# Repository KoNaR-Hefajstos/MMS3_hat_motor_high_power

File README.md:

# Hat Motor High Power

Dostosowany do 48V, ale można zmienić XXX żeby pracować na większym napięciu aż do 100V

Up to 100V 10A

# Dokumentacja
https://github.com/Themuse061/Moducard_System_Handbook

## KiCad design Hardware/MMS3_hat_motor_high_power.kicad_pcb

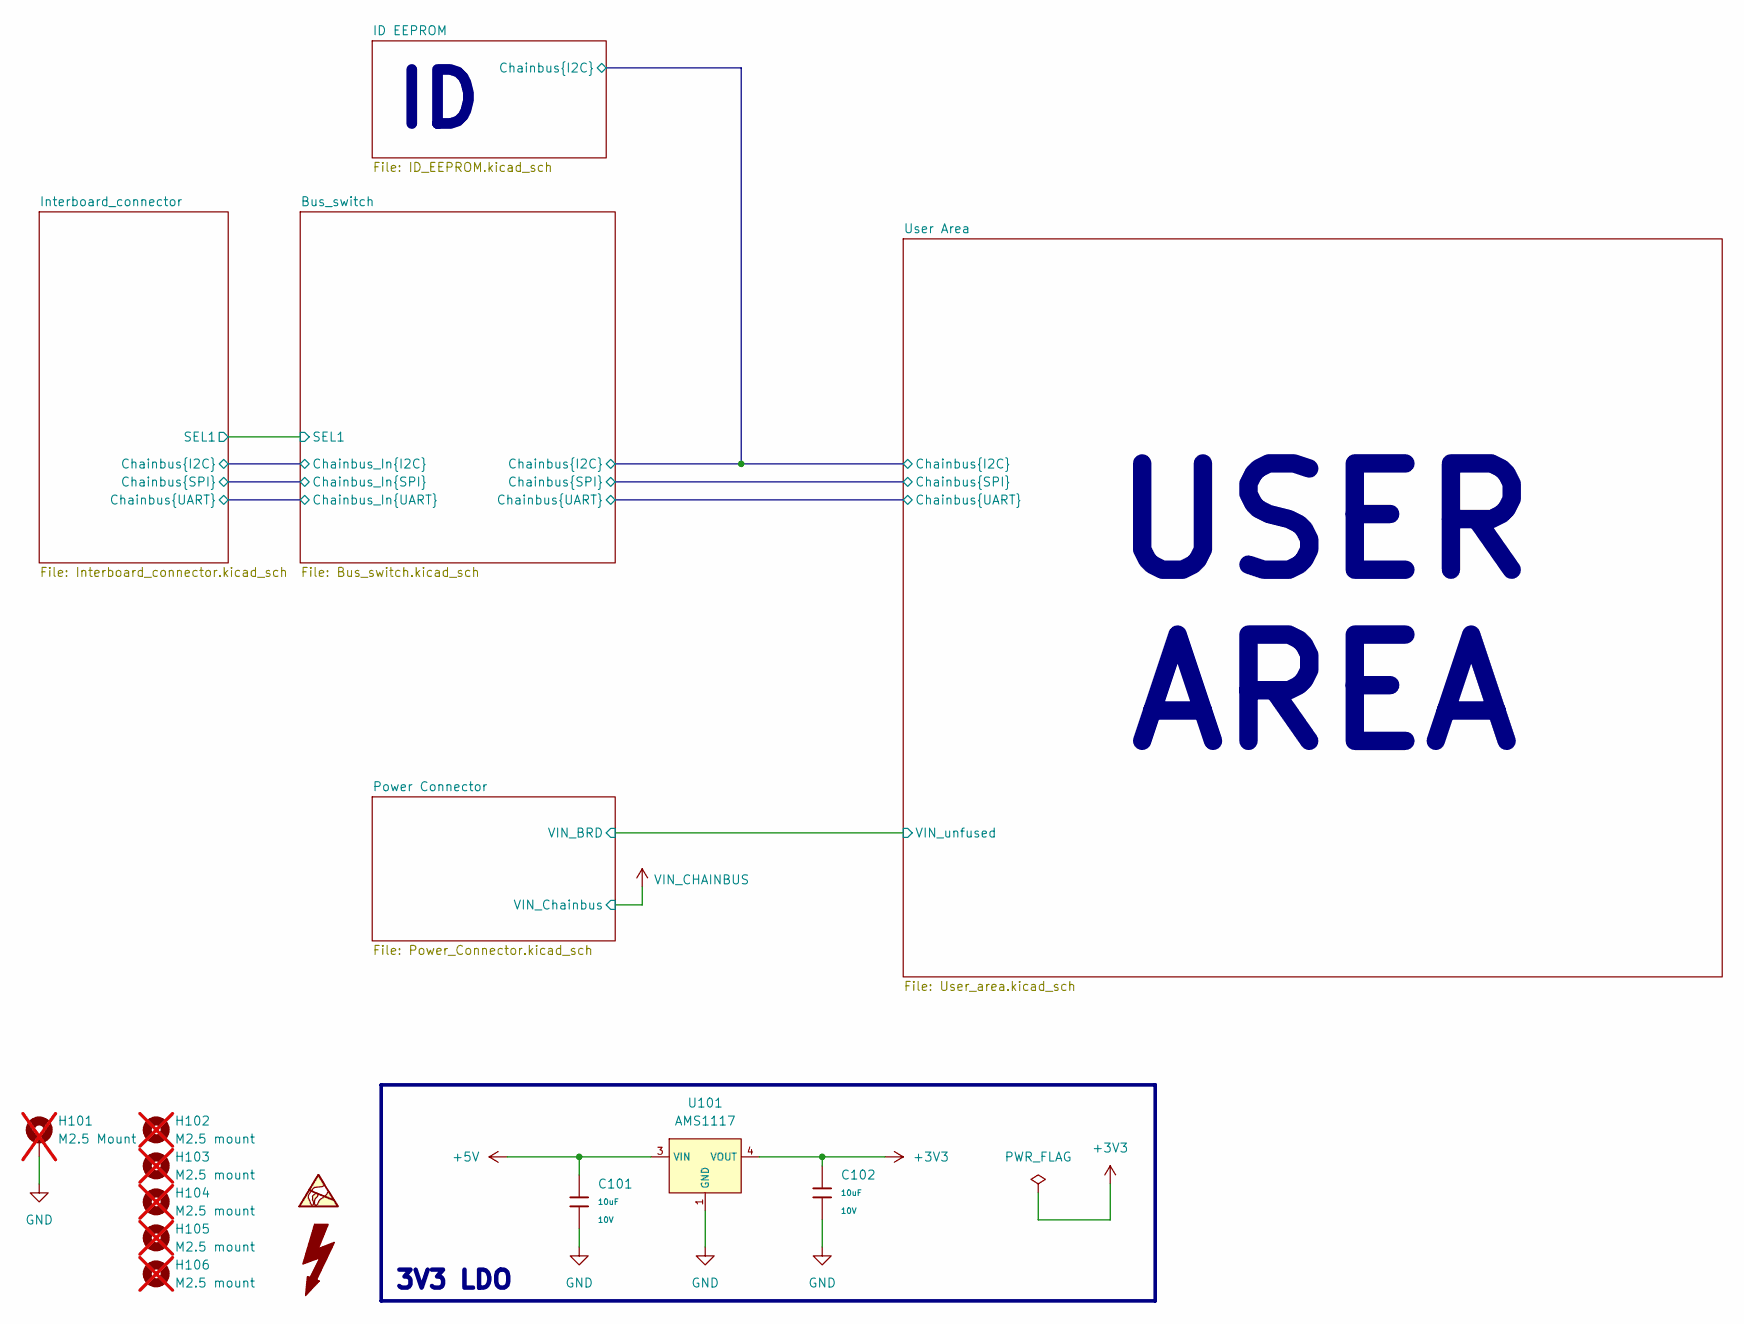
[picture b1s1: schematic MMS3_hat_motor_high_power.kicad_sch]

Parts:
C101, C102: 10uF; C_0603; Voltage Rated 10V; Tolerance ±10%; Part CL10A106KP8NNNC; LCSC C19702
H101: M2.5 Mount; MountingHole_2.7mm_M2.5_DIN965_Pad_TopOnly; not fitted
H102, H103, H104, H105, H106: M2.5 mount; MountingHole_2.7mm_M2.5; not fitted
U101: AMS1117; SOT-223-3_L6.5-W3.4-P2.30-LS7.0-BR; Output Voltage 3.3V; Dropout Voltage 1.3V@(800mA); Part AMS1117-3.3; LCSC C6186

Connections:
+3V3: C102.1, U101.2 (VOUT), U101.4 (VOUT); also elsewhere on the board
+5V: C101.1, U101.3 (VIN); also elsewhere on the board
GND: C101.2, C102.2, H101.1 (1_1), U101.1 (GND); also elsewhere on the board

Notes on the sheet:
USER AREA
3V3 LDO

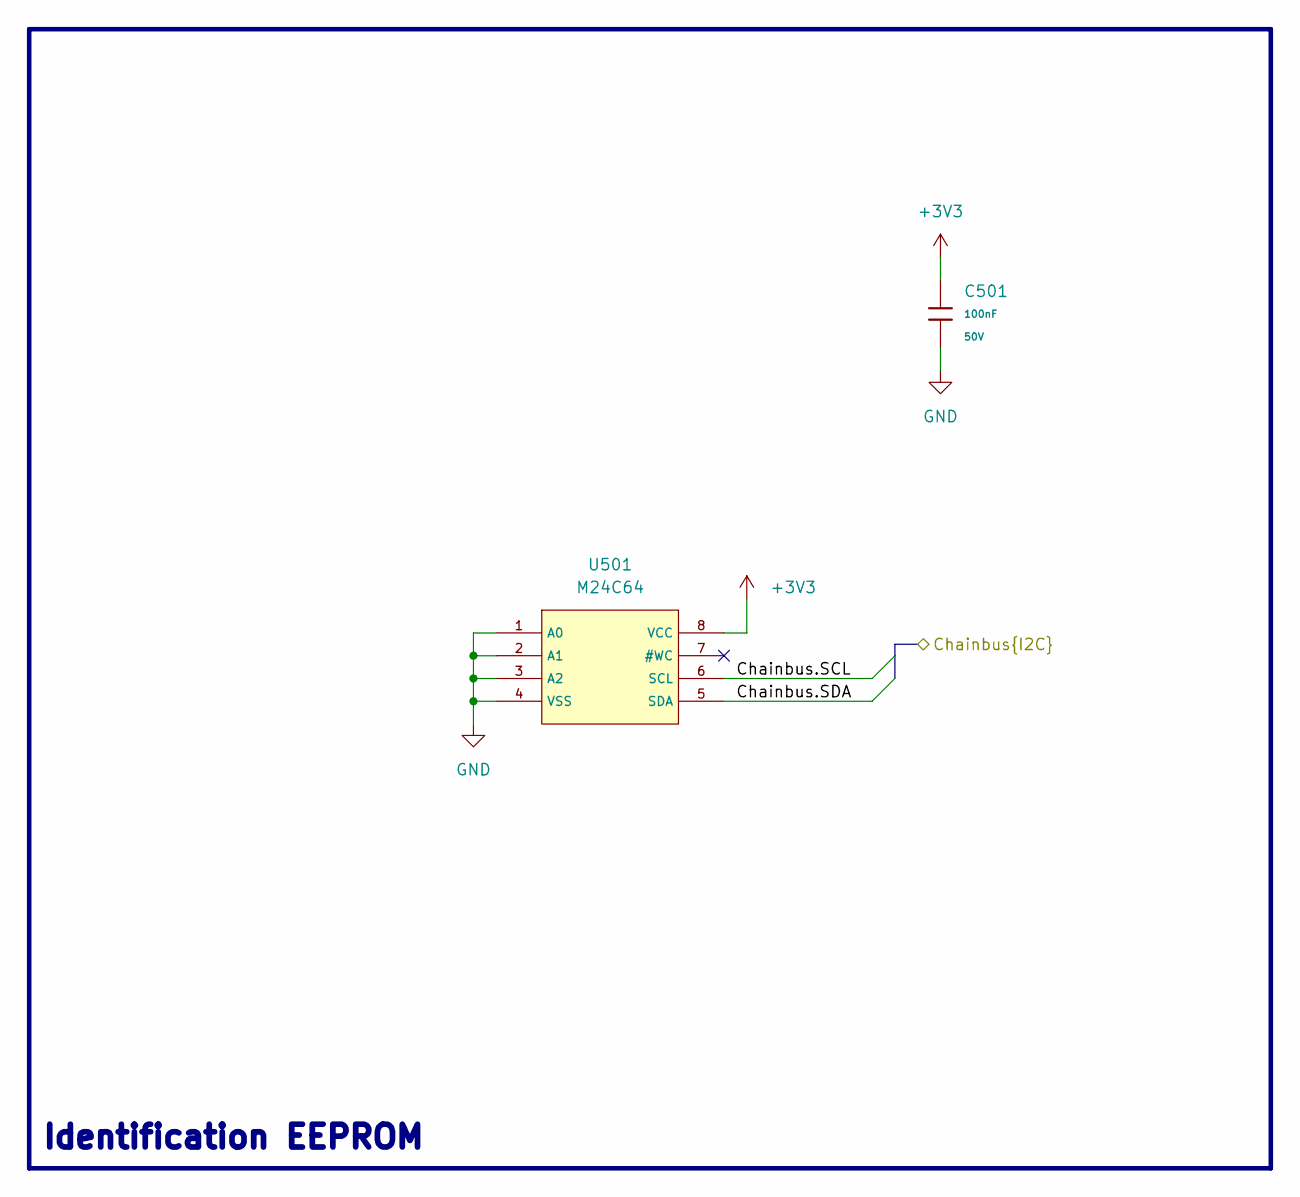
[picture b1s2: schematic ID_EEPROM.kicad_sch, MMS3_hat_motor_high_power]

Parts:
C501: 100nF; C_0603; Voltage Rated 50V; Tolerance ±10%; Part CC0603KRX7R9BB104; LCSC C14663
U501: M24C64; SOIC-8_L5.0-W4.0-P1.27-LS6.0-BL; Supply Voltage 1.8V~5.5V; Part M24C64-RMN6TP; LCSC C79988

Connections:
+3V3: C501.1, U501.8 (VCC); also elsewhere on the board
/Bus_switch/Chainbus.SCL: U501.6 (SCL); also elsewhere on the board
/Bus_switch/Chainbus.SDA: U501.5 (SDA); also elsewhere on the board
GND: C501.2, U501.1 (A0), U501.2 (A1), U501.3 (A2), U501.4 (VSS); also elsewhere on the board

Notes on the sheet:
Identification EEPROM

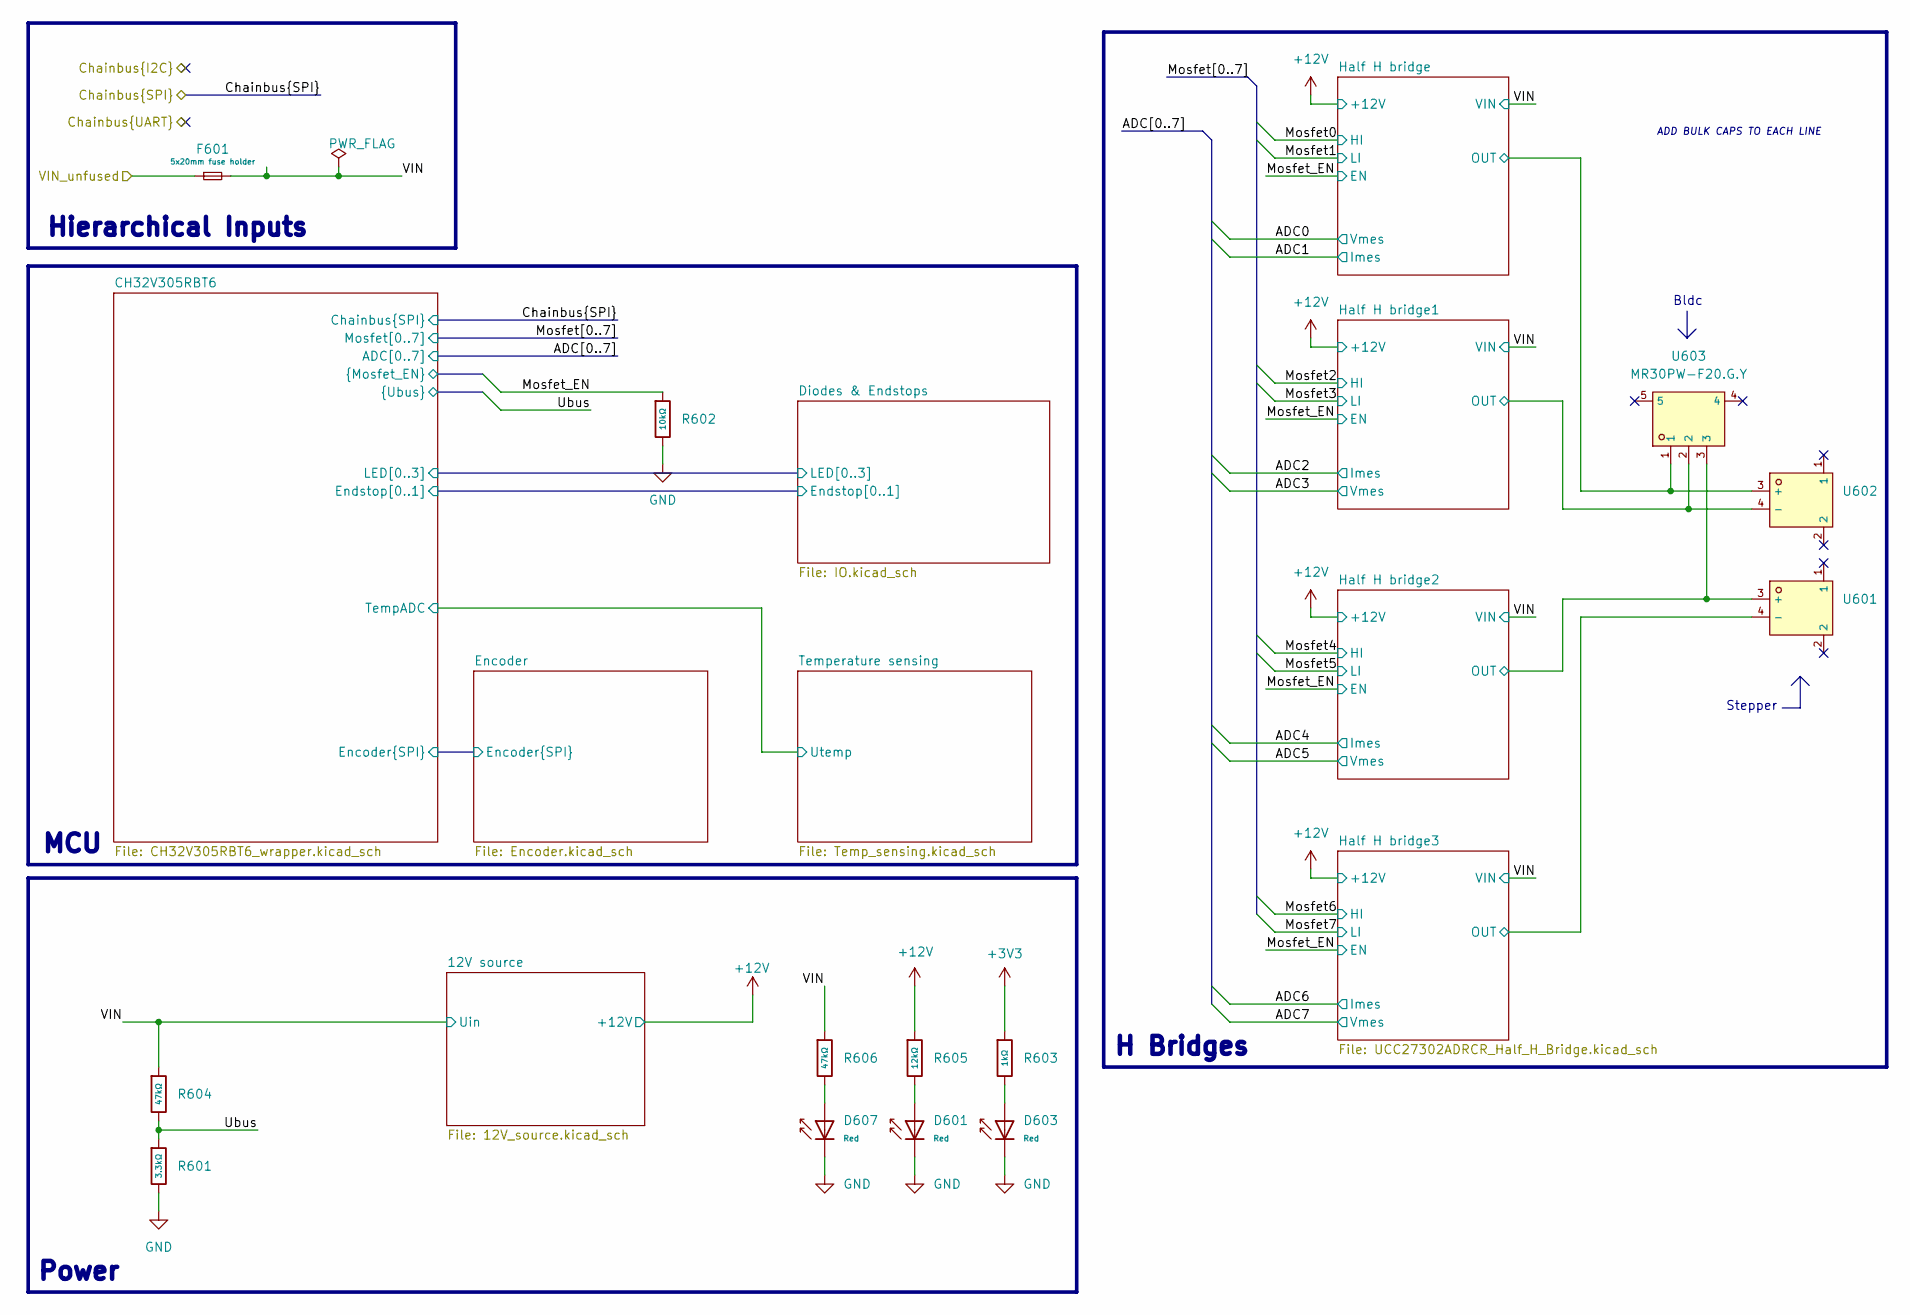
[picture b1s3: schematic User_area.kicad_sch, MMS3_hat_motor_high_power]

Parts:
D601, D603, D607: Red; D_0603; Part KT-0603R; LCSC C2286
F601: 01110506Z; Fuseholder_Clip-5x20mm_Littelfuse_111_Lateral_P18.80x5.00mm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; LCSC C206900
R601: 3.3kΩ; R_0402; Overload Voltage (Max) 50V; Tolerance ±1%; Part 0402WGF3301TCE; LCSC C25890
R602: 10kΩ; R_0402; Overload Voltage (Max) 50V; Tolerance ±1%; Part 0402WGF1002TCE; LCSC C25744
R603: 1kΩ; R_0402; Overload Voltage (Max) 50V; Tolerance ±1%; Part 0402WGF1001TCE; LCSC C11702
R604, R606: 47kΩ; R_0402; Overload Voltage (Max) 50V; Tolerance ±1%; Part 0402WGF4702TCE; LCSC C25792
R605: 12kΩ; R_0402; Overload Voltage (Max) 50V; Tolerance ±1%; Part 0402WGF1202TCE; LCSC C25752
U601, U602: XT60PW-F_C428722; C428722_TH_2P-XT60PW-F; LCSC C428722
U603: MR30PW-F20.G.Y; C19268035_CONN-TH_MR30PW-F; LCSC C19268035

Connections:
+3V3: R603.1; also elsewhere on the board
+12V: R605.1; also elsewhere on the board
/Power Connector/VIN_BRD: F601.1; also elsewhere on the board
/User Area/CH32V305RBT6/GPIOA0: R601.1, R604.2; also elsewhere on the board
/User Area/CH32V305RBT6/GPIOB12: R602.1; also elsewhere on the board
/User Area/Half H bridge1/HS: U602.4 (-), U603.2; also elsewhere on the board
/User Area/Half H bridge2/HS: U601.3 (+), U603.3; also elsewhere on the board
/User Area/Half H bridge3/HS: U601.4 (-); also elsewhere on the board
/User Area/Half H bridge/HS: U602.3 (+), U603.1; also elsewhere on the board
/User Area/VIN: F601.2, R604.1, R606.1; also elsewhere on the board
GND: D601.1, D603.1, D607.1, R601.2, R602.2; also elsewhere on the board
unnamed: D601.2, R605.2
unnamed: D603.2, R603.2
unnamed: D607.2, R606.2

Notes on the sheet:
Hierarchical Inputs
H Bridges
Power
MCU
Stepper
Bldc
ADD BULK CAPS TO EACH LINE

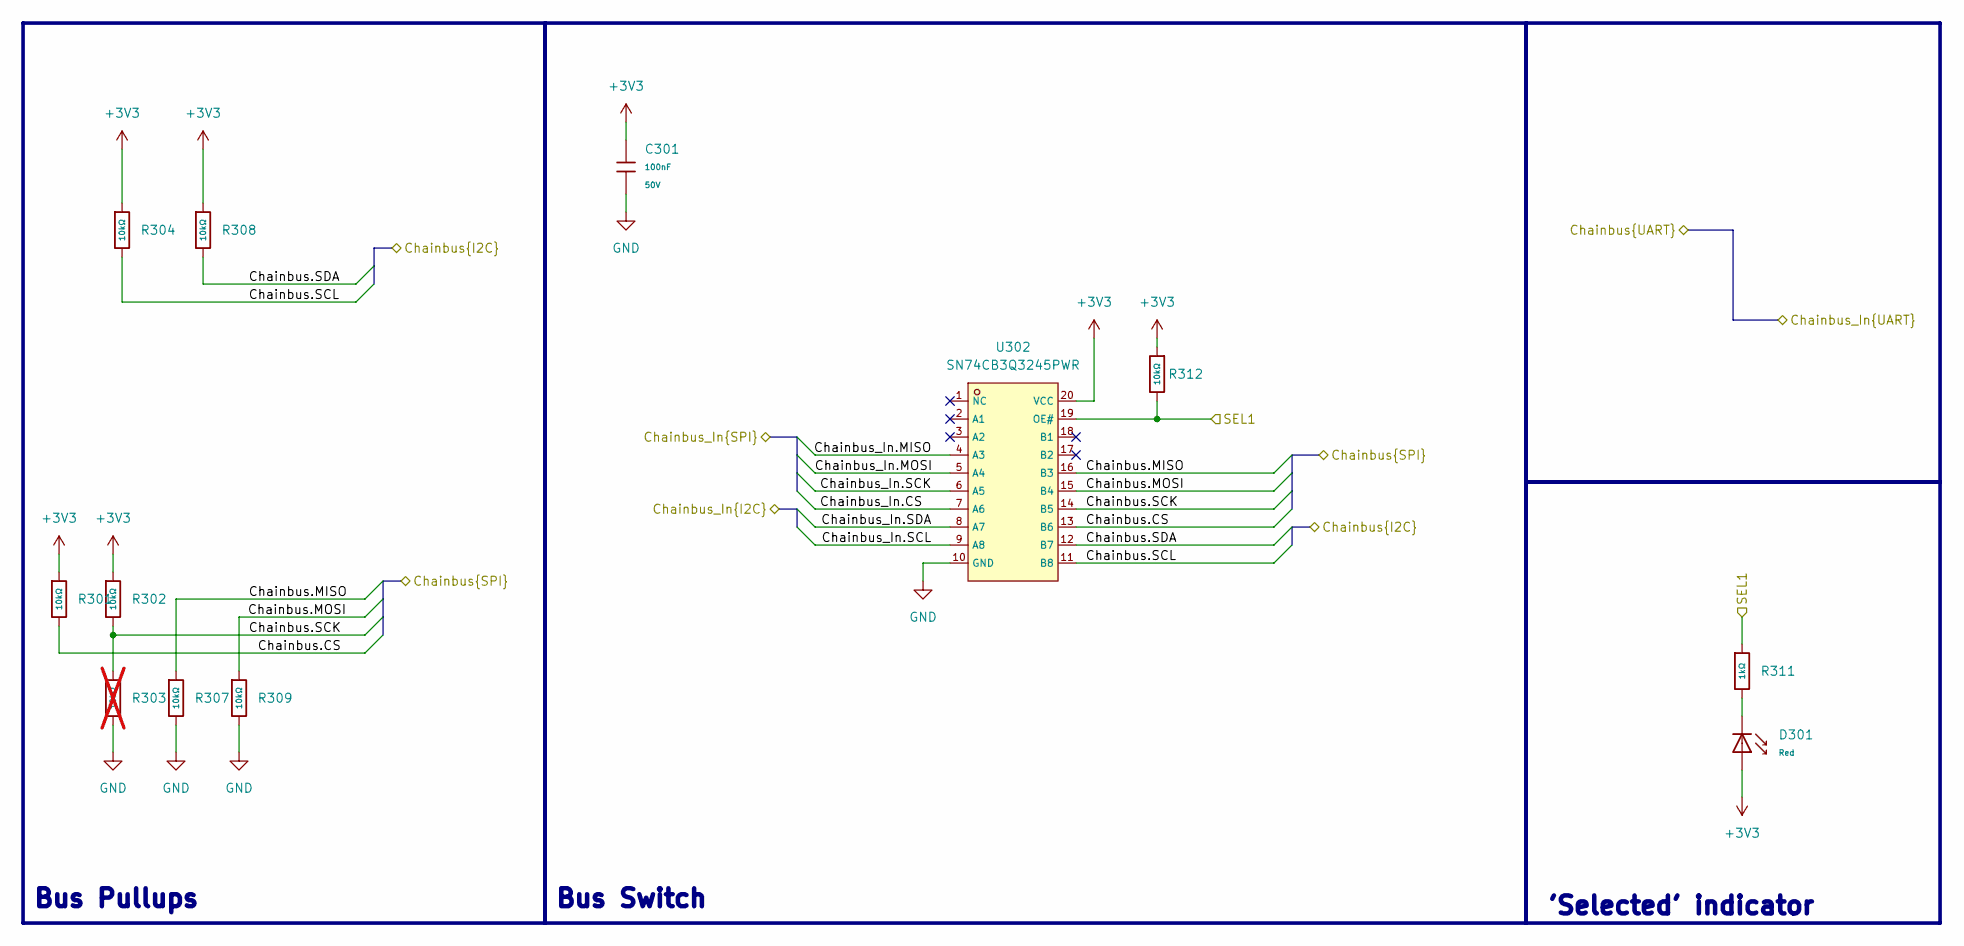
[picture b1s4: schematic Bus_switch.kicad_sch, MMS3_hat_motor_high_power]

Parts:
C301: 100nF; C_0603; Voltage Rated 50V; Tolerance ±10%; Part CC0603KRX7R9BB104; LCSC C14663
D301: Red; D_0603; Part KT-0603R; LCSC C2286
R301, R302, R304, R307, R308, R309, R312: 10kΩ; R_0603; Overload Voltage (Max) 75V; Tolerance ±1%; Part 0603WAF1002T5E; LCSC C25804
R303: 10kΩ; R_0603; Overload Voltage (Max) 75V; Tolerance ±1%; Part 0603WAF1002T5E; LCSC C25804; not fitted
R311: 1kΩ; R_0603; Overload Voltage (Max) 75V; Tolerance ±1%; Part 0603WAF1001T5E; LCSC C21190
U302: SN74CB3Q3245PWR; C470961_TSSOP-20_L6_5-W4_4-P0_65-LS6_4-BL; LCSC C470961

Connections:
+3V3: C301.1, D301.2, R301.1, R302.1, R304.1, R308.1, R312.1, U302.20 (VCC); also elsewhere on the board
/Bus_switch/Chainbus.SCL: R304.2, U302.11 (B8); also elsewhere on the board
/Bus_switch/Chainbus.SDA: R308.2, U302.12 (B7); also elsewhere on the board
/Bus_switch/Chainbus_In.CS: U302.7 (A6); also elsewhere on the board
/Bus_switch/Chainbus_In.MISO: U302.4 (A3); also elsewhere on the board
/Bus_switch/Chainbus_In.MOSI: U302.5 (A4); also elsewhere on the board
/Bus_switch/Chainbus_In.SCK: U302.6 (A5); also elsewhere on the board
/Bus_switch/Chainbus_In.SCL: U302.9 (A8); also elsewhere on the board
/Bus_switch/Chainbus_In.SDA: U302.8 (A7); also elsewhere on the board
/Bus_switch/SEL1: R311.1, R312.2, U302.19 (OE#); also elsewhere on the board
/User Area/Chainbus.CS: R301.2, U302.13 (B6); also elsewhere on the board
/User Area/Chainbus.MISO: R307.1, U302.16 (B3); also elsewhere on the board
/User Area/Chainbus.MOSI: R309.1, U302.15 (B4); also elsewhere on the board
/User Area/Chainbus.SCK: R302.2, R303.1, U302.14 (B5); also elsewhere on the board
GND: C301.2, R303.2, R307.2, R309.2, U302.10 (GND); also elsewhere on the board
unnamed: D301.1, R311.2

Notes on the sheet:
Bus Switch
'Selected' indicator
Bus Pullups

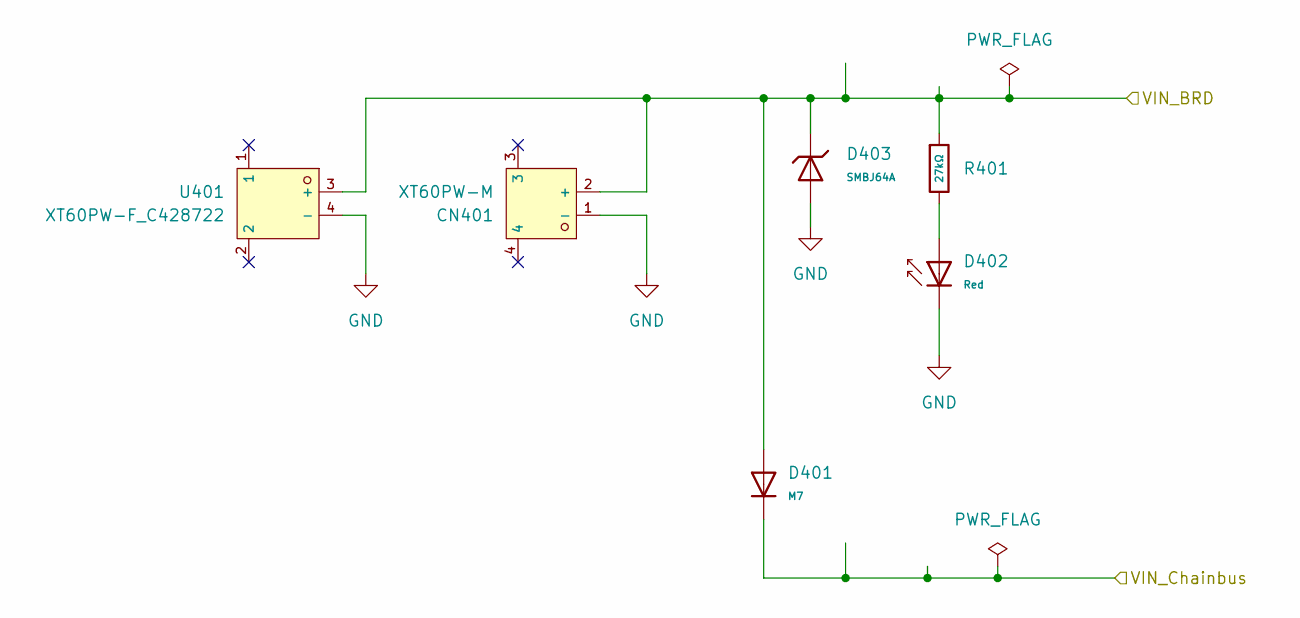
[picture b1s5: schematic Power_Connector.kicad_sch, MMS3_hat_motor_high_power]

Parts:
CN401: XT60PW-M; C98732_CONN-TH_XT60PW-M; LCSC C98732
D401: M7; D_SMA; Forward Voltage (Vf@If) 1.1V@1A; Reverse Voltage (Vr) 1kV; Part M7; LCSC C95872
D402: Red; D_0603; Part KT-0603R; LCSC C2286
D403: SMBJ64A; D_SMB; Part SMBJ64A; LCSC C19077594
R401: 27kΩ; R_0603; Overload Voltage (Max) 75V; Tolerance ±1%; Part 0603WAF2702T5E; LCSC C22967
U401: XT60PW-F_C428722; C428722_TH_2P-XT60PW-F; LCSC C428722

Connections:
/Power Connector/VIN_BRD: CN401.2 (+), D401.2, D403.1, R401.1, U401.3 (+); also elsewhere on the board
GND: CN401.1 (-), D402.1, D403.2, U401.4 (-); also elsewhere on the board
unnamed: D402.2, R401.2
VIN_CHAINBUS: D401.1; also elsewhere on the board

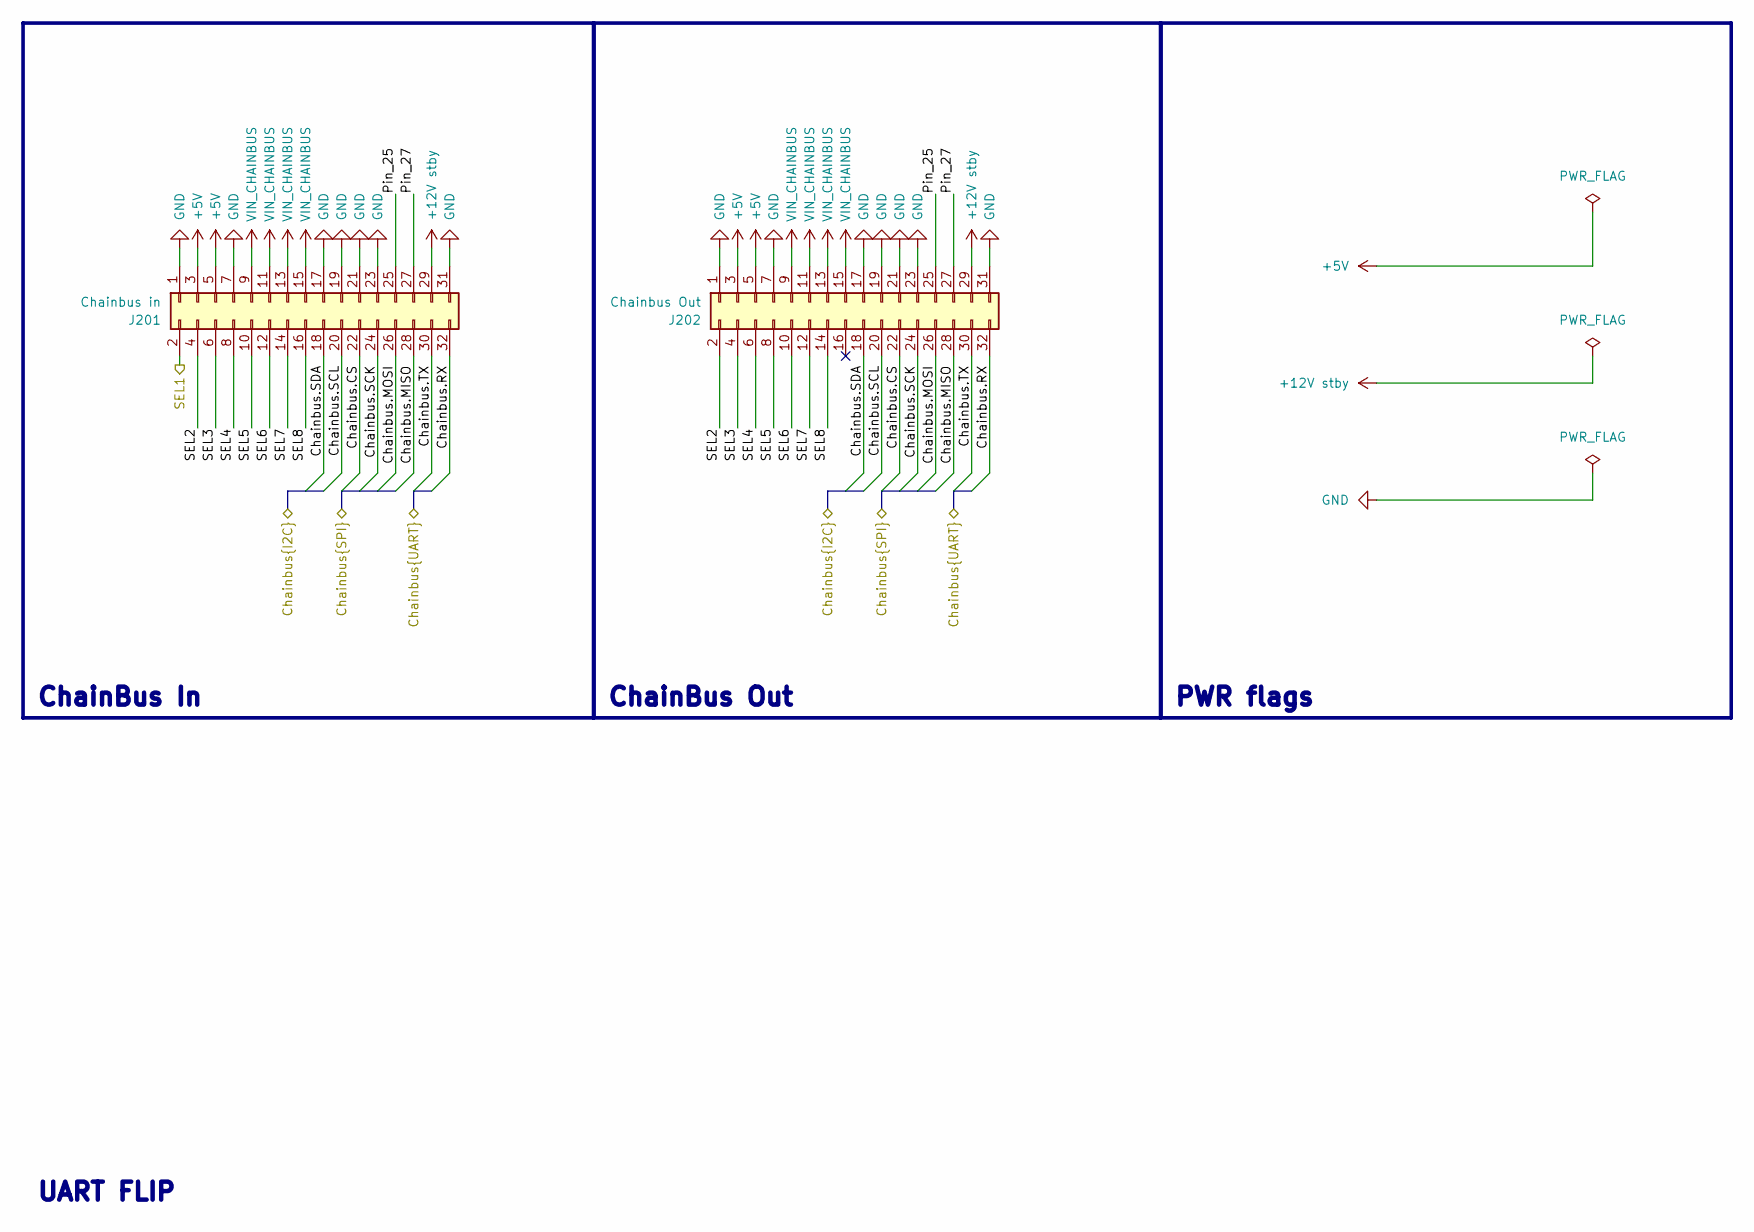
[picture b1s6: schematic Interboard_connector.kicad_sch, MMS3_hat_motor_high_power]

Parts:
J201: Chainbus in; PinHeader_2x16_P2.54mm_Vertical_SMD
J202: Chainbus Out; PinSocket_2x16_P2.54mm_Vertical_SMD

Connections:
+5V: J201.3, J201.5, J202.3, J202.5; also elsewhere on the board
+12V stby: J201.29, J202.29
/Bus_switch/Chainbus_In.CS: J201.22, J202.22; also elsewhere on the board
/Bus_switch/Chainbus_In.MISO: J201.28, J202.28; also elsewhere on the board
/Bus_switch/Chainbus_In.MOSI: J201.26, J202.26; also elsewhere on the board
/Bus_switch/Chainbus_In.RX: J201.32, J202.32
/Bus_switch/Chainbus_In.SCK: J201.24, J202.24; also elsewhere on the board
/Bus_switch/Chainbus_In.SCL: J201.20, J202.20; also elsewhere on the board
/Bus_switch/Chainbus_In.SDA: J201.18, J202.18; also elsewhere on the board
/Bus_switch/Chainbus_In.TX: J201.30, J202.30
/Bus_switch/SEL1: J201.2; also elsewhere on the board
/Interboard_connector/Pin_25: J201.25, J202.25
/Interboard_connector/Pin_27: J201.27, J202.27
/Interboard_connector/SEL2: J201.4, J202.2
/Interboard_connector/SEL3: J201.6, J202.4
/Interboard_connector/SEL4: J201.8, J202.6
/Interboard_connector/SEL5: J201.10, J202.8
/Interboard_connector/SEL6: J201.12, J202.10
/Interboard_connector/SEL7: J201.14, J202.12
/Interboard_connector/SEL8: J201.16, J202.14
GND: J201.1, J201.7, J201.17, J201.19, J201.21, J201.23, J201.31, J202.1, J202.7, J202.17, J202.19, J202.21, J202.23, J202.31; also elsewhere on the board
VIN_CHAINBUS: J201.9, J201.11, J201.13, J201.15, J202.9, J202.11, J202.13, J202.15; also elsewhere on the board

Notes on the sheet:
ChainBus In
UART FLIP
PWR flags
ChainBus Out

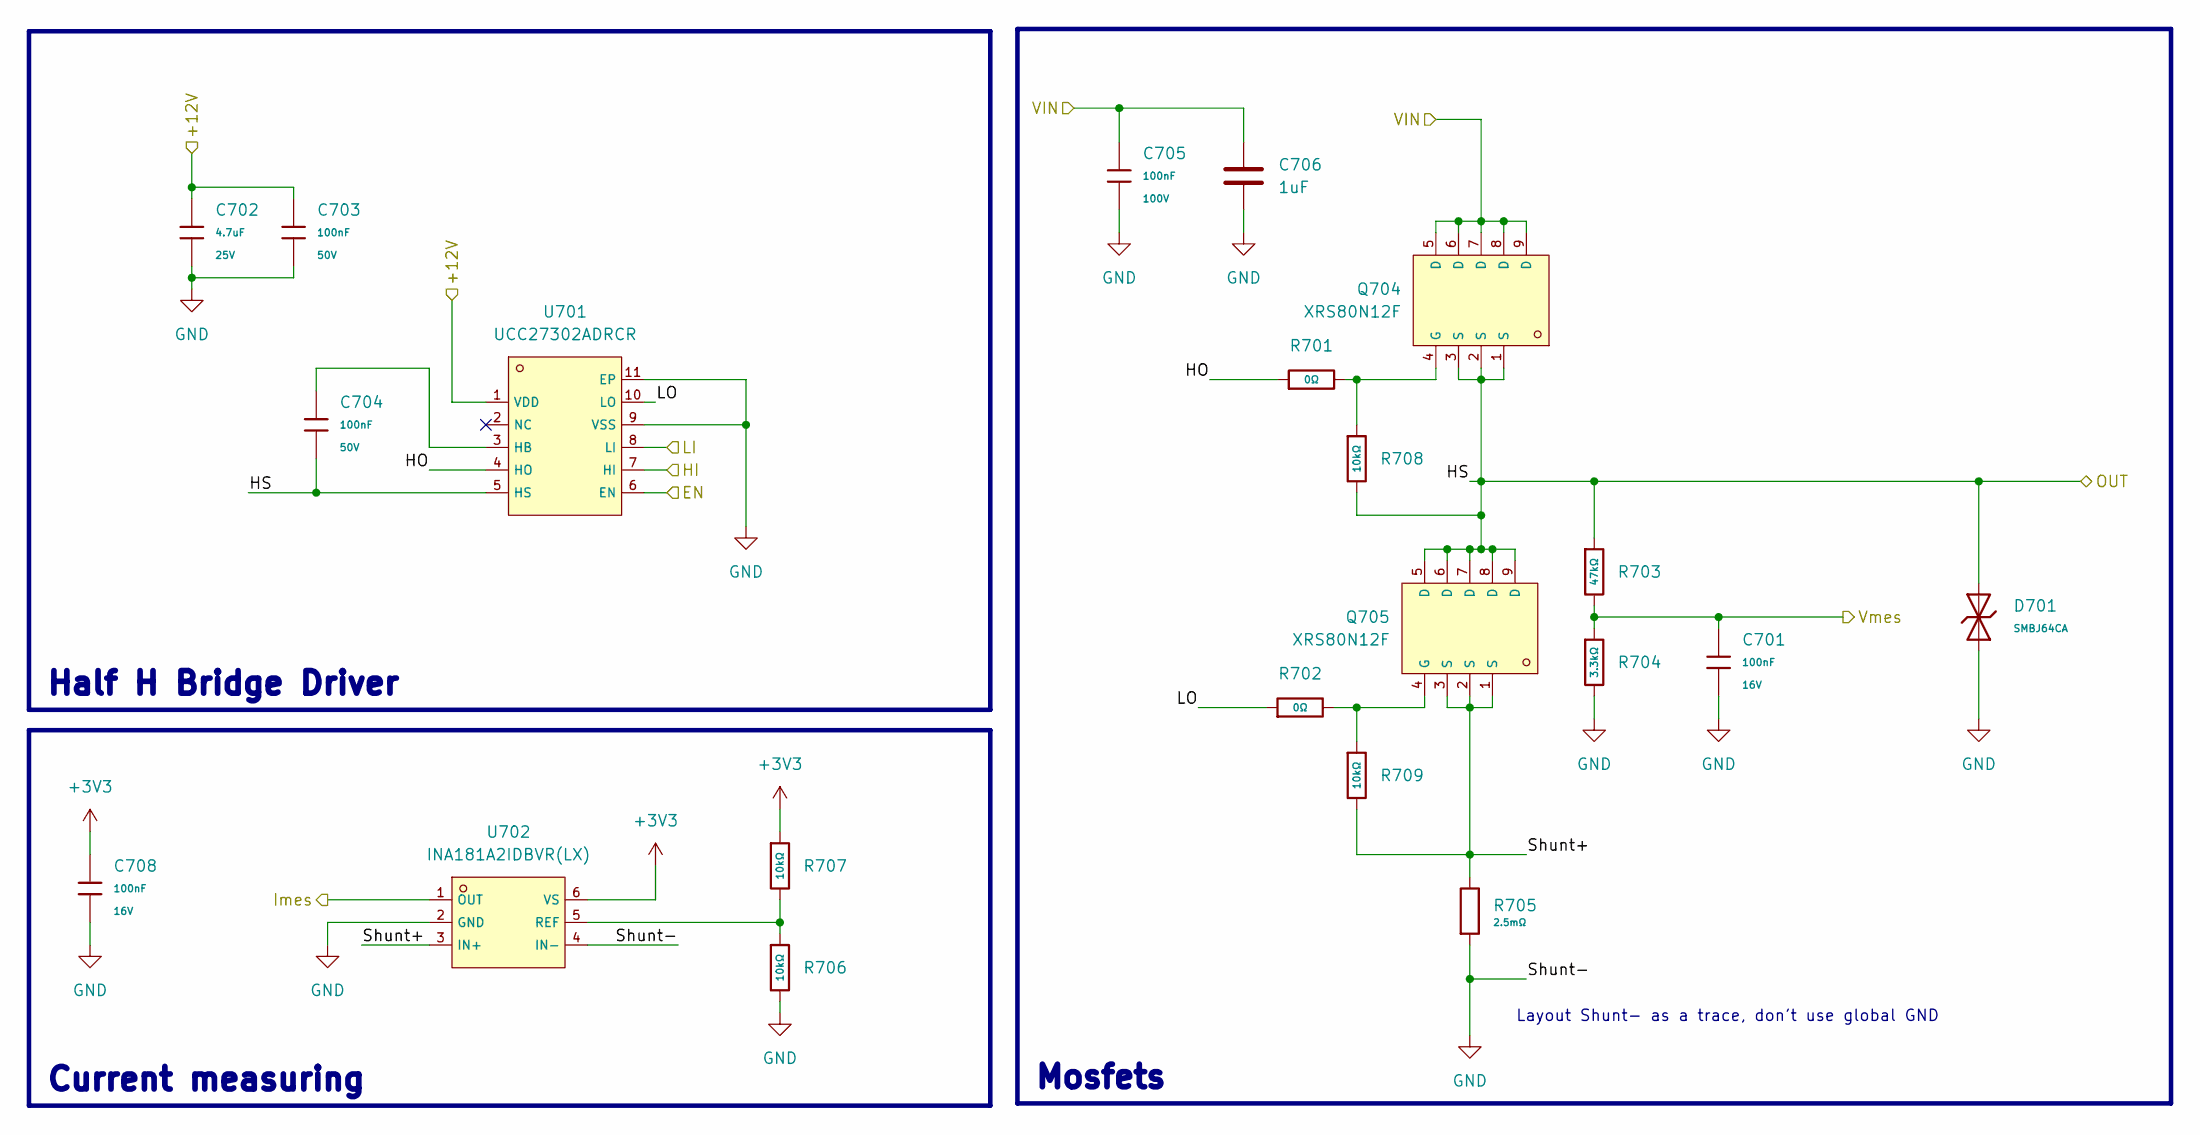
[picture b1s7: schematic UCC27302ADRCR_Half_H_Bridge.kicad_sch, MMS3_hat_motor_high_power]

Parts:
C701, C708: 100nF; C_0402; Voltage Rated 16V; Tolerance ±10%; Part CL05B104KO5NNNC; LCSC C1525
C702: 4.7uF; C_0805; Voltage Rated 25V; Tolerance ±10%; Part CL21A475KAQNNNE; LCSC C1779
C703, C704: 100nF; C_0603; Voltage Rated 50V; Tolerance ±10%; Part CC0603KRX7R9BB104; LCSC C14663
C705: 100nF; C_0805; Voltage Rated 100V; Tolerance ±10%; Part CL21B104KCFNNNE; LCSC C28233
C706: 1uF; C_0805
D701: SMBJ64CA; D_SMB; Breakdown Voltage 78.6V; Part SMBJ64CA; LCSC C41376099
Q704, Q705: XRS80N12F; C42457090_DFN-8_L5_8-W4_9-P1_27-LS6_1-BL; LCSC C42457090
R701, R702: 0Ω; R_0402; Overload Voltage (Max) 50V; Tolerance ±1%; Part 0402WGF0000TCE; LCSC C17168
R703: 47kΩ; R_0402; Overload Voltage (Max) 50V; Tolerance ±1%; Part 0402WGF4702TCE; LCSC C25792
R704: 3.3kΩ; R_0402; Overload Voltage (Max) 50V; Tolerance ±1%; Part 0402WGF3301TCE; LCSC C25890
R705: FRM252WFR0025TN; R_2512_6332Metric_Pad1.40x3.35mm_HandSolder
R706, R707, R708, R709: 10kΩ; R_0402; Overload Voltage (Max) 50V; Tolerance ±1%; Part 0402WGF1002TCE; LCSC C25744
U701: UCC27302ADRCR; C50092311_VSON-10_L3_0-W3_0-P0_50-TL-EP; LCSC C50092311
U702: INA181A2IDBVR(LX); C53198613_SOT-23-6_L2_9-W1_6-P0_95-LS2_8-BL; LCSC C53198613

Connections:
+3V3: C708.1, R707.1, U702.6 (VS); also elsewhere on the board
+12V: C702.1, C703.1, U701.1 (VDD); also elsewhere on the board
/User Area/ADC0: C701.1, R703.2, R704.1; also elsewhere on the board
/User Area/ADC1: U702.1 (OUT); also elsewhere on the board
/User Area/CH32V305RBT6/GPIOB12: U701.6 (EN); also elsewhere on the board
/User Area/Half H bridge/HO: R701.1, U701.4 (HO)
/User Area/Half H bridge/HS: C704.2, D701.2, Q704.1 (S), Q704.2 (S), Q704.3 (S), Q705.5 (D), Q705.6 (D), Q705.7 (D), Q705.8 (D), Q705.9 (D), R703.1, R708.2, U701.5 (HS); also elsewhere on the board
/User Area/Half H bridge/LO: R702.1, U701.10 (LO)
/User Area/Half H bridge/Shunt+: Q705.1 (S), Q705.2 (S), Q705.3 (S), R705.1, R709.2, U702.3 (IN+)
/User Area/Mosfet0: U701.7 (HI); also elsewhere on the board
/User Area/Mosfet1: U701.8 (LI); also elsewhere on the board
/User Area/VIN: C705.1, C706.1, Q704.5 (D), Q704.6 (D), Q704.7 (D), Q704.8 (D), Q704.9 (D); also elsewhere on the board
GND: C701.2, C702.2, C703.2, C705.2, C706.2, C708.2, D701.1, R704.2, R705.2, R706.2, U701.9 (VSS), U701.11 (EP), U702.2 (GND), U702.4 (IN-); also elsewhere on the board
unnamed: Q704.4 (G), R701.2, R708.1
unnamed: Q705.4 (G), R702.2, R709.1
unnamed: C704.1, U701.3 (HB)
unnamed: R706.1, R707.2, U702.5 (REF)

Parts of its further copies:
C801, C901, C1001: 4.7uF; C_0805; Voltage Rated 25V; Tolerance ±10%; Part CL21A475KAQNNNE; LCSC C1779
C802, C804, C902, C904, C1002, C1004: 100nF; C_0603; Voltage Rated 50V; Tolerance ±10%; Part CC0603KRX7R9BB104; LCSC C14663
C803, C808, C903, C908, C1003, C1008: 100nF; C_0402; Voltage Rated 16V; Tolerance ±10%; Part CL05B104KO5NNNC; LCSC C1525
C805, C905, C1005: 100nF; C_0805; Voltage Rated 100V; Tolerance ±10%; Part CL21B104KCFNNNE; LCSC C28233
C806, C906, C1006: 1uF; C_0805
D801, D901, D1001: SMBJ64CA; D_SMB; Breakdown Voltage 78.6V; Part SMBJ64CA; LCSC C41376099
Q801, Q802, Q901, Q902, Q1001, Q1002: XRS80N12F; C42457090_DFN-8_L5_8-W4_9-P1_27-LS6_1-BL; LCSC C42457090
R801, R803, R901, R903, R1001, R1003: 0Ω; R_0402; Overload Voltage (Max) 50V; Tolerance ±1%; Part 0402WGF0000TCE; LCSC C17168
R802, R902, R1002: 47kΩ; R_0402; Overload Voltage (Max) 50V; Tolerance ±1%; Part 0402WGF4702TCE; LCSC C25792
R804, R904, R1004: 3.3kΩ; R_0402; Overload Voltage (Max) 50V; Tolerance ±1%; Part 0402WGF3301TCE; LCSC C25890
R805, R905, R1005: FRM252WFR0025TN; R_2512_6332Metric_Pad1.40x3.35mm_HandSolder
R806, R807, R808, R809, R906, R907, R908, R909, R1006, R1007, R1008, R1009: 10kΩ; R_0402; Overload Voltage (Max) 50V; Tolerance ±1%; Part 0402WGF1002TCE; LCSC C25744
U801, U901, U1001: UCC27302ADRCR; C50092311_VSON-10_L3_0-W3_0-P0_50-TL-EP; LCSC C50092311
U802, U902, U1002: INA181A2IDBVR(LX); C53198613_SOT-23-6_L2_9-W1_6-P0_95-LS2_8-BL; LCSC C53198613

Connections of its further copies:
+3V3: C808.1, C908.1, C1008.1, R807.1, R907.1, R1007.1, U802.6 (VS), U902.6 (VS), U1002.6 (VS); also elsewhere on the board
+12V: C801.1, C802.1, C901.1, C902.1, C1001.1, C1002.1, U801.1 (VDD), U901.1 (VDD), U1001.1 (VDD); also elsewhere on the board
/User Area/ADC2: U802.1 (OUT); also elsewhere on the board
/User Area/ADC3: C803.1, R802.2, R804.1; also elsewhere on the board
/User Area/ADC4: U902.1 (OUT); also elsewhere on the board
/User Area/ADC5: C903.1, R902.2, R904.1; also elsewhere on the board
/User Area/ADC6: U1002.1 (OUT); also elsewhere on the board
/User Area/ADC7: C1003.1, R1002.2, R1004.1; also elsewhere on the board
/User Area/CH32V305RBT6/GPIOB12: U801.6 (EN), U901.6 (EN), U1001.6 (EN); also elsewhere on the board
/User Area/Half H bridge1/HO: R801.1, U801.4 (HO)
/User Area/Half H bridge1/HS: C804.2, D801.2, Q801.5 (D), Q801.6 (D), Q801.7 (D), Q801.8 (D), Q801.9 (D), Q802.1 (S), Q802.2 (S), Q802.3 (S), R802.1, R808.2, U801.5 (HS); also elsewhere on the board
/User Area/Half H bridge1/LO: R803.1, U801.10 (LO)
/User Area/Half H bridge1/Shunt+: Q801.1 (S), Q801.2 (S), Q801.3 (S), R805.1, R809.2, U802.3 (IN+)
/User Area/Half H bridge2/HO: R901.1, U901.4 (HO)
/User Area/Half H bridge2/HS: C904.2, D901.2, Q901.5 (D), Q901.6 (D), Q901.7 (D), Q901.8 (D), Q901.9 (D), Q902.1 (S), Q902.2 (S), Q902.3 (S), R902.1, R908.2, U901.5 (HS); also elsewhere on the board
/User Area/Half H bridge2/LO: R903.1, U901.10 (LO)
/User Area/Half H bridge2/Shunt+: Q901.1 (S), Q901.2 (S), Q901.3 (S), R905.1, R909.2, U902.3 (IN+)
/User Area/Half H bridge3/HO: R1001.1, U1001.4 (HO)
/User Area/Half H bridge3/HS: C1004.2, D1001.2, Q1001.5 (D), Q1001.6 (D), Q1001.7 (D), Q1001.8 (D), Q1001.9 (D), Q1002.1 (S), Q1002.2 (S), Q1002.3 (S), R1002.1, R1008.2, U1001.5 (HS); also elsewhere on the board
/User Area/Half H bridge3/LO: R1003.1, U1001.10 (LO)
/User Area/Half H bridge3/Shunt+: Q1001.1 (S), Q1001.2 (S), Q1001.3 (S), R1005.1, R1009.2, U1002.3 (IN+)
/User Area/Mosfet2: U801.7 (HI); also elsewhere on the board
/User Area/Mosfet3: U801.8 (LI); also elsewhere on the board
/User Area/Mosfet4: U901.7 (HI); also elsewhere on the board
/User Area/Mosfet5: U901.8 (LI); also elsewhere on the board
/User Area/Mosfet6: U1001.7 (HI); also elsewhere on the board
/User Area/Mosfet7: U1001.8 (LI); also elsewhere on the board
/User Area/VIN: C805.1, C806.1, C905.1, C906.1, C1005.1, C1006.1, Q802.5 (D), Q802.6 (D), Q802.7 (D), Q802.8 (D), Q802.9 (D), Q902.5 (D), Q902.6 (D), Q902.7 (D), Q902.8 (D), Q902.9 (D), Q1002.5 (D), Q1002.6 (D), Q1002.7 (D), Q1002.8 (D), Q1002.9 (D); also elsewhere on the board
GND: C801.2, C802.2, C803.2, C805.2, C806.2, C808.2, C901.2, C902.2, C903.2, C905.2, C906.2, C908.2, C1001.2, C1002.2, C1003.2, C1005.2, C1006.2, C1008.2, D801.1, D901.1, D1001.1, R804.2, R805.2, R806.2, R904.2, R905.2, R906.2, R1004.2, R1005.2, R1006.2, U801.9 (VSS), U801.11 (EP), U802.2 (GND), U802.4 (IN-), U901.9 (VSS), U901.11 (EP), U902.2 (GND), U902.4 (IN-), U1001.9 (VSS), U1001.11 (EP), U1002.2 (GND), U1002.4 (IN-); also elsewhere on the board
unnamed: Q801.4 (G), R803.2, R809.1
unnamed: Q802.4 (G), R801.2, R808.1
unnamed: Q901.4 (G), R903.2, R909.1
unnamed: Q902.4 (G), R901.2, R908.1
unnamed: Q1001.4 (G), R1003.2, R1009.1
unnamed: Q1002.4 (G), R1001.2, R1008.1
unnamed: C804.1, U801.3 (HB)
unnamed: R806.1, R807.2, U802.5 (REF)
unnamed: C904.1, U901.3 (HB)
unnamed: R906.1, R907.2, U902.5 (REF)
unnamed: C1004.1, U1001.3 (HB)
unnamed: R1006.1, R1007.2, U1002.5 (REF)

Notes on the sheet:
Half H Bridge Driver
Current measuring
Mosfets
Layout Shunt- as a trace, don't use global GND
